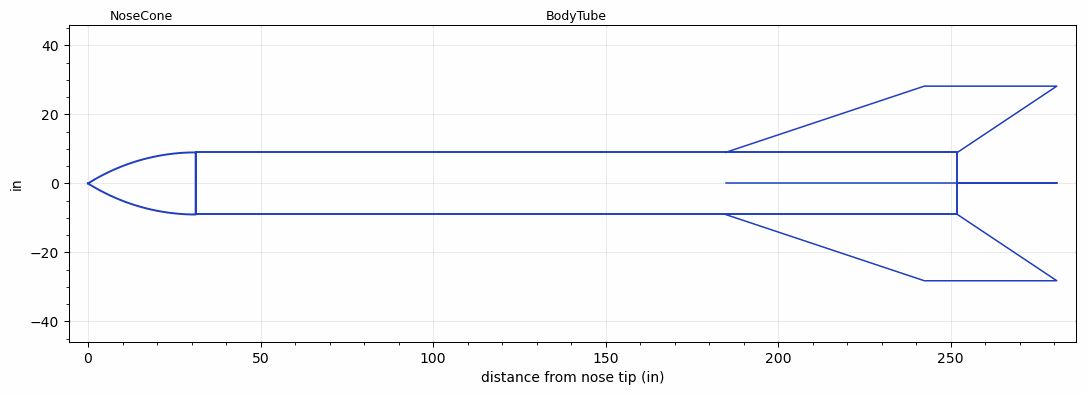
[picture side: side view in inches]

<RASAeroDocument>
 <FileVersion>2</FileVersion>
 <RocketDesign>
  <NoseCone>
   <Length>31.2</Length>
   <Diameter>18</Diameter>
   <Shape>Tangent Ogive</Shape>
   <Location>0</Location>
  </NoseCone>
  <BodyTube>
   <Length>220.8</Length>
   <Diameter>18</Diameter>
   <Location>31.2</Location>
   <Fin>
    <Count>4</Count>
    <Chord>67.2</Chord>
    <Span>19.2</Span>
    <SweepDistance>57.6</SweepDistance>
    <TipChord>38.4</TipChord>
    <Thickness>2.4</Thickness>
    <Location>67.2</Location>
    <AirfoilSection>Square</AirfoilSection>
   </Fin>
  </BodyTube>
  <Surface>Smooth (Zero Roughness)</Surface>
  <ModifiedBarrowman>False</ModifiedBarrowman>
  <Turbulence>False</Turbulence>
  <UseBooster1>False</UseBooster1>
  <UseBooster2>False</UseBooster2>
 </RocketDesign>
 <LaunchSite>
  <Altitude>0</Altitude>
  <Pressure>0</Pressure>
  <RodAngle>0</RodAngle>
  <RodLength>4</RodLength>
  <Temperature>74</Temperature>
  <WindSpeed>0</WindSpeed>
 </LaunchSite>
 <Recovery>
  <Altitude1>1000</Altitude1>
  <Altitude2>1000</Altitude2>
  <DeviceType1>None</DeviceType1>
  <DeviceType2>None</DeviceType2>
  <Event1>False</Event1>
  <Event2>False</Event2>
  <Size1>1</Size1>
  <Size2>1</Size2>
  <EventType1>None</EventType1>
  <EventType2>None</EventType2>
  <CD1>1.33</CD1>
  <CD2>1.33</CD2>
 </Recovery>
</RASAeroDocument>
